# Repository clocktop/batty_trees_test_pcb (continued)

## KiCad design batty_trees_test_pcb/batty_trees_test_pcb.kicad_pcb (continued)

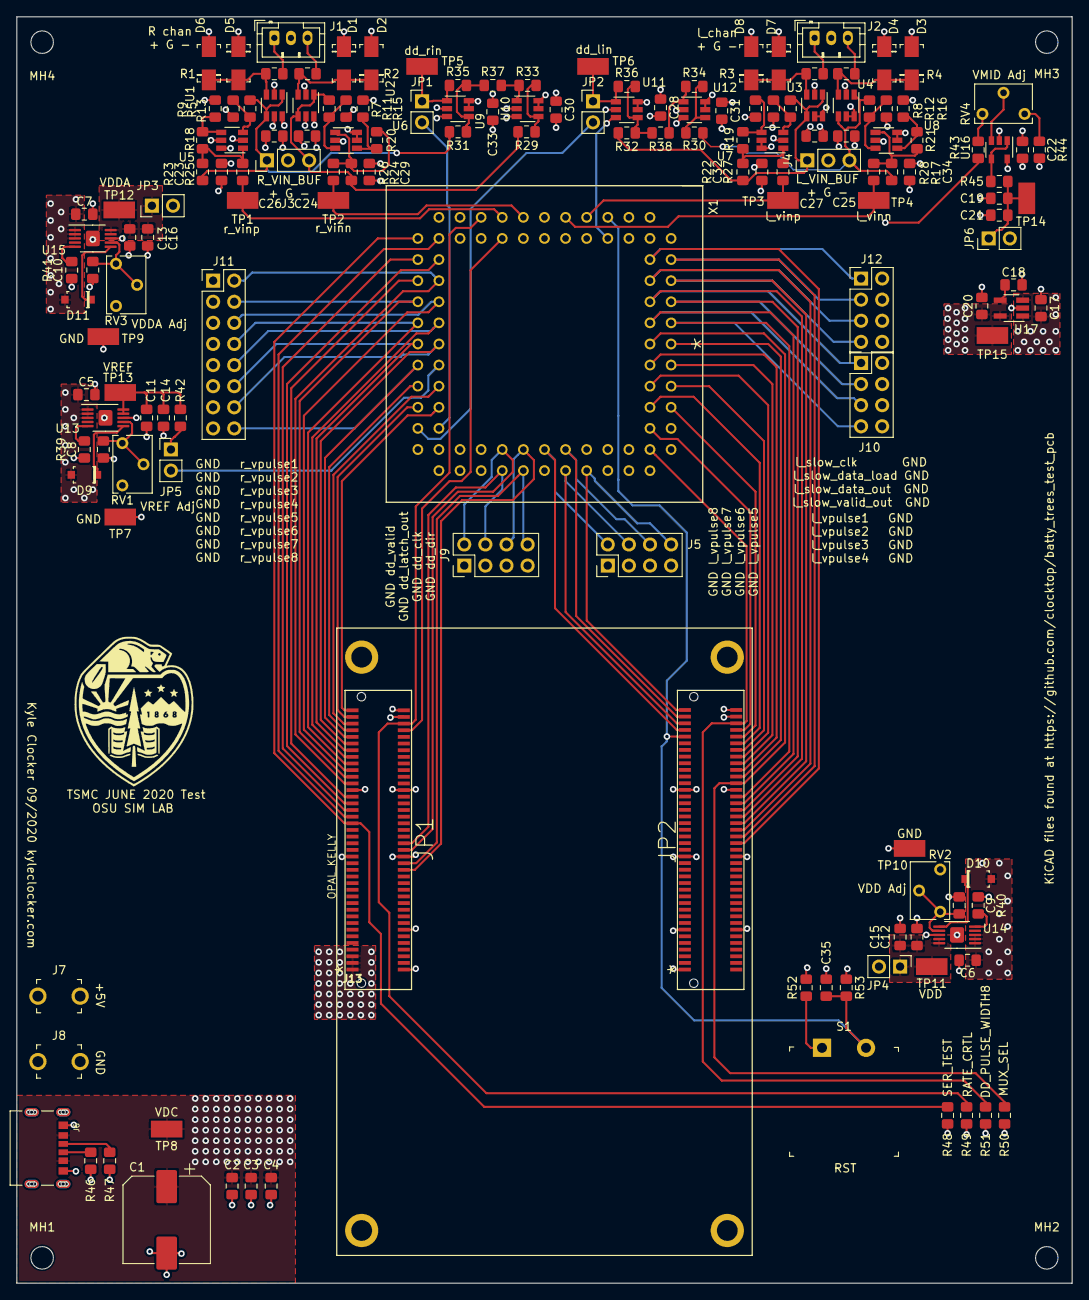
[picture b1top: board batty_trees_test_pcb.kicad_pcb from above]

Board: 4 copper layers, 127.0 x 152.3 mm, 160 parts (0 on the bottom side), 113 nets.

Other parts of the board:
MH1, MH2, MH3, MH4: MountingHole_2.7mm_M2.5

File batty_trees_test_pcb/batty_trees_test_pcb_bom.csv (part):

"Source:","C:\Users\clock\OneDrive\Documents\DOE_Bats\TSMC_JUN_2020\batty_trees_test_pcb\batty_trees_test_pcb\batty_trees_test_pcb.sch"
"Date:","8/31/2020 6:11:37 PM"
"Tool:","Eeschema (5.1.5)-3"
"Generator:","C:\Program Files\KiCad\bin\scripting\plugins/bom_csv_grouped_by_value.py"
"Component Count:","141"

"Individual Components:"

"Item","Qty","Reference(s)","Value","LibPart","Footprint","Datasheet","Category","DK_Datasheet_Link","DK_Detail_Page","Description","Digi-Key-PN","Digi-Key_PN","Family","MPN","Manufacturer","Status"
"","","C1","47uF","Device:CP1_Small","Capacitor_SMD:CP_Elec_10x10","~","","","","","","EEE-FK1K470P","","","",""
"","","C2","4.7uF","Device:C_Small","Capacitor_SMD:C_0805_2012Metric_Pad1.15x1.40mm_HandSolder","~","","","","","","490-14466-1-ND","","","",""
"","","C3","0.47uF","Device:C_Small","Capacitor_SMD:C_0805_2012Metric_Pad1.15x1.40mm_HandSolder","~","","","","","","399-9247-1-ND","","","",""
"","","C4","0.1uF","Device:C_Small","Capacitor_SMD:C_0805_2012Metric_Pad1.15x1.40mm_HandSolder","~","","","","","","399-8000-1-ND","","","",""
"","","C5","4.7uF","Device:C_Small","Capacitor_SMD:C_0805_2012Metric_Pad1.15x1.40mm_HandSolder","~","","","","","","490-14466-1-ND","","","",""
"","","C6","4.7uF","Device:C_Small","Capacitor_SMD:C_0805_2012Metric_Pad1.15x1.40mm_HandSolder","~","","","","","","490-14466-1-ND","","","",""
"","","C7","4.7uF","Device:C_Small","Capacitor_SMD:C_0805_2012Metric_Pad1.15x1.40mm_HandSolder","~","","","","","","490-14466-1-ND","","","",""
"","","C8","0.47uF","Device:C_Small","Capacitor_SMD:C_0805_2012Metric_Pad1.15x1.40mm_HandSolder","~","","","","","","399-9247-1-ND","","","",""
"","","C9","0.47uF","Device:C_Small","Capacitor_SMD:C_0805_2012Metric_Pad1.15x1.40mm_HandSolder","~","","","","","","399-9247-1-ND","","","",""
"","","C10","0.47uF","Device:C_Small","Capacitor_SMD:C_0805_2012Metric_Pad1.15x1.40mm_HandSolder","~","","","","","","399-9247-1-ND","","","",""
"","","C11","4.7uF","Device:C_Small","Capacitor_SMD:C_0805_2012Metric_Pad1.15x1.40mm_HandSolder","~","","","","","","490-14466-1-ND","","","",""
"","","C12","4.7uF","Device:C_Small","Capacitor_SMD:C_0805_2012Metric_Pad1.15x1.40mm_HandSolder","~","","","","","","490-14466-1-ND","","","",""
"","","C13","4.7uF","Device:C_Small","Capacitor_SMD:C_0805_2012Metric_Pad1.15x1.40mm_HandSolder","~","","","","","","490-14466-1-ND","","","",""
"","","C14","0.1uF","Device:C_Small","Capacitor_SMD:C_0805_2012Metric_Pad1.15x1.40mm_HandSolder","~","","","","","","399-8000-1-ND","","","",""
"","","C15","0.1uF","Device:C_Small","Capacitor_SMD:C_0805_2012Metric_Pad1.15x1.40mm_HandSolder","~","","","","","","399-8000-1-ND","","","",""
"","","C16","0.1uF","Device:C_Small","Capacitor_SMD:C_0805_2012Metric_Pad1.15x1.40mm_HandSolder","~","","","","","","399-8000-1-ND","","","",""
"","","C17","4.7uF","Device:C_Small","Capacitor_SMD:C_0805_2012Metric_Pad1.15x1.40mm_HandSolder","~","","","","","","490-14466-1-ND","","","",""
"","","C18","0.1uF","Device:C_Small","Capacitor_SMD:C_0805_2012Metric_Pad1.15x1.40mm_HandSolder","~","","","","","","399-8000-1-ND","","","",""
"","","C19","4.7uF","Device:C_Small","Capacitor_SMD:C_0805_2012Metric_Pad1.15x1.40mm_HandSolder","~","","","","","","490-14466-1-ND","","","",""
"","","C20","4.7uF","Device:C_Small","Capacitor_SMD:C_0805_2012Metric_Pad1.15x1.40mm_HandSolder","~","","","","","","490-14466-1-ND","","","",""
"","","C21","0.1uF","Device:C_Small","Capacitor_SMD:C_0805_2012Metric_Pad1.15x1.40mm_HandSolder","~","","","","","","399-8000-1-ND","","","",""
"","","C22","0.1uF","Device:C_Small","Capacitor_SMD:C_0805_2012Metric_Pad1.15x1.40mm_HandSolder","~","","","","","","399-8000-1-ND","","","",""
"","","C23","0.1uF","Device:C_Small","Capacitor_SMD:C_0805_2012Metric_Pad1.15x1.40mm_HandSolder","~","","","","","","399-8000-1-ND","","","",""
"","","C24","0.1uF","Device:C_Small","Capacitor_SMD:C_0805_2012Metric_Pad1.15x1.40mm_HandSolder","~","","","","","","399-8000-1-ND","","","",""
"","","C25","0.1uF","Device:C_Small","Capacitor_SMD:C_0805_2012Metric_Pad1.15x1.40mm_HandSolder","~","","","","","","399-8000-1-ND","","","",""
"","","C26","0.1uF","Device:C_Small","Capacitor_SMD:C_0805_2012Metric_Pad1.15x1.40mm_HandSolder","~","","","","","","399-8000-1-ND","","","",""
"","","C27","0.1uF","Device:C_Small","Capacitor_SMD:C_0805_2012Metric_Pad1.15x1.40mm_HandSolder","~","","","","","","399-8000-1-ND","","","",""
"","","C28","0.1uF","Device:C_Small","Capacitor_SMD:C_0805_2012Metric_Pad1.15x1.40mm_HandSolder","~","","","","","","399-8000-1-ND","","","",""
"","","C29","0.1uF","Device:C_Small","Capacitor_SMD:C_0805_2012Metric_Pad1.15x1.40mm_HandSolder","~","","","","","","399-8000-1-ND","","","",""
"","","C30","0.1uF","Device:C_Small","Capacitor_SMD:C_0805_2012Metric_Pad1.15x1.40mm_HandSolder","~","","","","","","399-8000-1-ND","","","",""
"","","C31","0.1uF","Device:C_Small","Capacitor_SMD:C_0805_2012Metric_Pad1.15x1.40mm_HandSolder","~","","","","","","399-8000-1-ND","","","",""
"","","C32","0.1uF","Device:C_Small","Capacitor_SMD:C_0805_2012Metric_Pad1.15x1.40mm_HandSolder","~","","","","","","399-8000-1-ND","","","",""
"","","C33","0.1uF","Device:C_Small","Capacitor_SMD:C_0805_2012Metric_Pad1.15x1.40mm_HandSolder","~","","","","","","399-8000-1-ND","","","",""
"","","C34","0.1uF","Device:C_Small","Capacitor_SMD:C_0805_2012Metric_Pad1.15x1.40mm_HandSolder","~","","","","","","399-8000-1-ND","","","",""
"","","C35","0.1uF","Device:C_Small","Capacitor_SMD:C_0805_2012Metric_Pad1.15x1.40mm_HandSolder","~","","","","","","399-8000-1-ND","","","",""
"","","D1","B240A-13-F","dk_Diodes-Rectifiers-Single:B240A-13-F","digikey-footprints:DO-214AC","https://www.diodes.com/assets/Datasheets/ds13004.pdf","Discrete Semiconductor Products","https://www.diodes.com/assets/Datasheets/ds13004.pdf","/product-detail/en/diodes-incorporated/B240A-13-F/B240A-FDICT-ND/717810","DIODE SCHOTTKY 40V 2A SMA","","B240A-FDICT-ND","Diodes - Rectifiers - Single","B240A-13-F","Diodes Incorporated","Active"
"","","D2","B240A-13-F","dk_Diodes-Rectifiers-Single:B240A-13-F","digikey-footprints:DO-214AC","https://www.diodes.com/assets/Datasheets/ds13004.pdf","Discrete Semiconductor Products","https://www.diodes.com/assets/Datasheets/ds13004.pdf","/product-detail/en/diodes-incorporated/B240A-13-F/B240A-FDICT-ND/717810","DIODE SCHOTTKY 40V 2A SMA","","B240A-FDICT-ND","Diodes - Rectifiers - Single","B240A-13-F","Diodes Incorporated","Active"
"","","D3","B240A-13-F","dk_Diodes-Rectifiers-Single:B240A-13-F","digikey-footprints:DO-214AC","https://www.diodes.com/assets/Datasheets/ds13004.pdf","Discrete Semiconductor Products","https://www.diodes.com/assets/Datasheets/ds13004.pdf","/product-detail/en/diodes-incorporated/B240A-13-F/B240A-FDICT-ND/717810","DIODE SCHOTTKY 40V 2A SMA","","B240A-FDICT-ND","Diodes - Rectifiers - Single","B240A-13-F","Diodes Incorporated","Active"
"","","D4","B240A-13-F","dk_Diodes-Rectifiers-Single:B240A-13-F","digikey-footprints:DO-214AC","https://www.diodes.com/assets/Datasheets/ds13004.pdf","Discrete Semiconductor Products","https://www.diodes.com/assets/Datasheets/ds13004.pdf","/product-detail/en/diodes-incorporated/B240A-13-F/B240A-FDICT-ND/717810","DIODE SCHOTTKY 40V 2A SMA","","B240A-FDICT-ND","Diodes - Rectifiers - Single","B240A-13-F","Diodes Incorporated","Active"
"","","D5","B240A-13-F","dk_Diodes-Rectifiers-Single:B240A-13-F","digikey-footprints:DO-214AC","https://www.diodes.com/assets/Datasheets/ds13004.pdf","Discrete Semiconductor Products","https://www.diodes.com/assets/Datasheets/ds13004.pdf","/product-detail/en/diodes-incorporated/B240A-13-F/B240A-FDICT-ND/717810","DIODE SCHOTTKY 40V 2A SMA","","B240A-FDICT-ND","Diodes - Rectifiers - Single","B240A-13-F","Diodes Incorporated","Active"
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
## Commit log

2020-08-13 started kicad project
2020-08-18 power and references section 95% done
2020-08-19 Finished off Power section and made up AFE schematic
2020-08-26 wired up chip to fpga on schematic and begininng to do layout
2020-08-29 more layout work ~90% finished
2020-09-01 Layout finished and gerbers generated checking for DFM
2020-09-01 all componenets updated with digikey pn bom generated
2020-09-01 final ordering revision
